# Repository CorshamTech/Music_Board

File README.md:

# SS-30 Music Board

This is a rough recreation of the Newtech Computer Systems model 68 music board.  No atttempt
was made to make it look exactly like the original, but it is 100% compatible and uses the
same components as the original.

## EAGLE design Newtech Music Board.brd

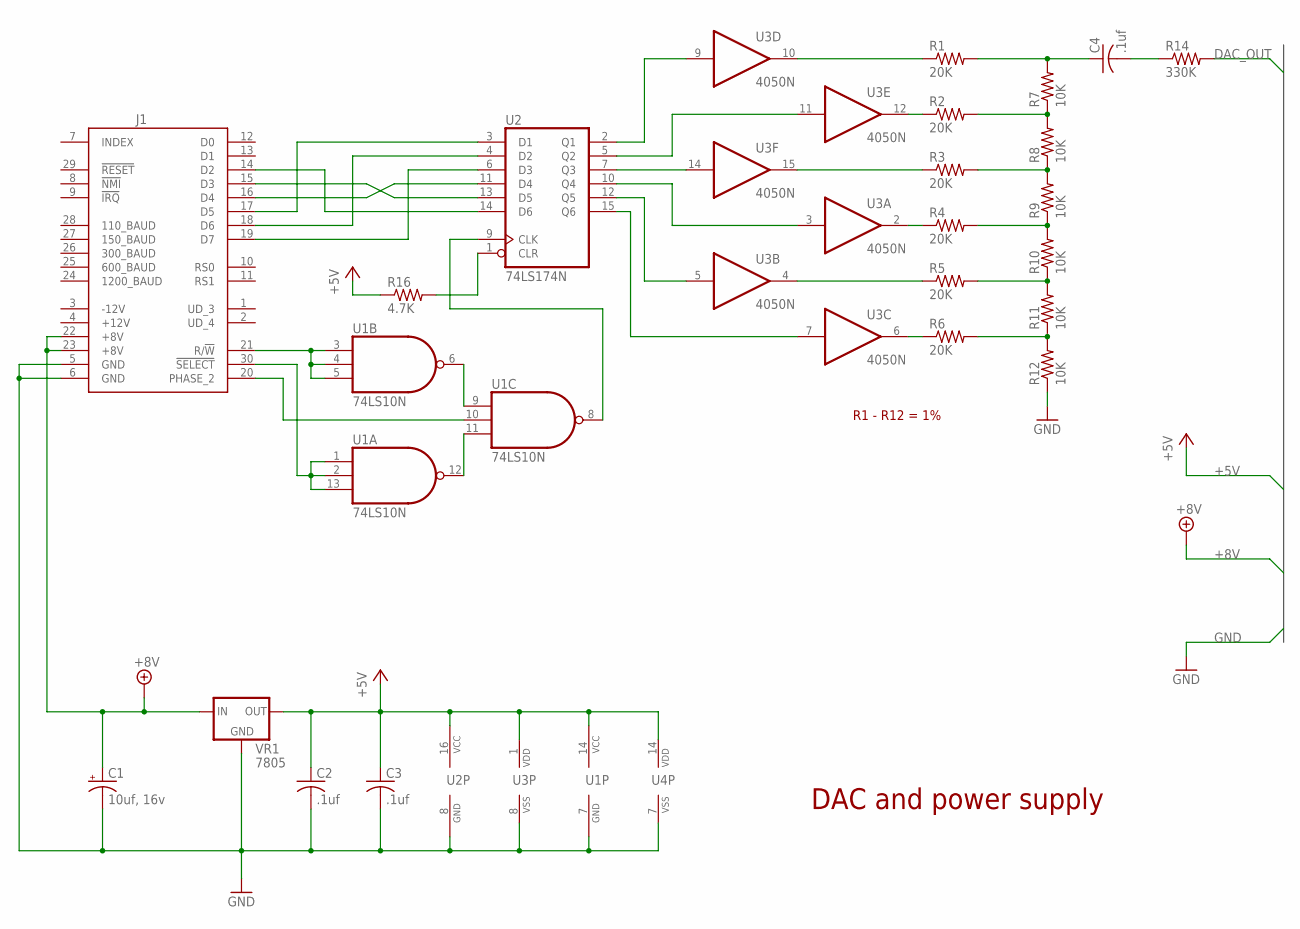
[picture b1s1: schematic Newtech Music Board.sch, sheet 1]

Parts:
C1: 10uf, 16v; E2,5-6
C2, C3: .1uf; C025-025X050
C4: .1uf; C025-024X044
J1: SS-30_BOARD_CONNECTOR
R1, R2, R3, R4, R5, R6: 20K; 0204/7
R7, R8, R9, R10, R11, R12: 10K; 0204/7
R14: 330K; 0204/7
R16: 4.7K; 0204/7
U1: 74LS10N; DIL14
U2: 74LS174N; DIL16
U3: 4050N; DIL16
U4: 4069N; DIL14
VR1: 7805; 78XXL

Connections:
!SELECT: J1.30 (!SELECT), U1.1 (I0), U1.2 (I1), U1.13 (I2)
+5V: C2.1, C3.1, R16.1, U1.14 (VCC), U2.16 (VCC), U3.1 (VDD), U4.14 (VDD), VR1.OUT
+8V: C1.+, J1.22 (+8V), J1.23 (+8V), VR1.IN; also elsewhere on the board
+12V: J1.4 (+12V)
-12V: J1.3 (-12V)
DAC_OUT: R14.2; also elsewhere on the board
GND: C1.-, C2.2, C3.2, J1.5 (GND), J1.6 (GND), R12.1, U1.7 (GND), U2.8 (GND), U3.8 (VSS), U4.7 (VSS), VR1.GND; also elsewhere on the board
unnamed: J1.19 (D7), U2.6 (D3)
unnamed: J1.18 (D6), U2.4 (D2)
unnamed: J1.17 (D5), U2.3 (D1)
unnamed: U1.6 (O), U1.9 (I0)
unnamed: U1.11 (I2), U1.12 (O)
unnamed: J1.16 (D4), U2.11 (D4)
unnamed: J1.15 (D3), U2.13 (D5)
unnamed: J1.14 (D2), U2.14 (D6)
unnamed: U2.2 (Q1), U3.9 (I)
unnamed: U2.5 (Q2), U3.11 (I)
unnamed: U2.7 (Q3), U3.14 (I)
unnamed: U2.10 (Q4), U3.3 (I)
unnamed: U2.12 (Q5), U3.5 (I)
unnamed: U2.15 (Q6), U3.7 (I)
unnamed: U1.8 (O), U2.9 (CLK)
unnamed: R16.2, U2.1 (CLR)
unnamed: R1.1, U3.10 (O)
unnamed: R2.1, U3.12 (O)
unnamed: R3.1, U3.15 (O)
unnamed: R4.1, U3.2 (O)
unnamed: R5.1, U3.4 (O)
unnamed: R6.1, U3.6 (O)
unnamed: R2.2, R7.1, R8.2
unnamed: R3.2, R8.1, R9.2
unnamed: R4.2, R9.1, R10.2
unnamed: R5.2, R10.1, R11.2
unnamed: R6.2, R11.1, R12.2
unnamed: C4.1, R1.2, R7.2
unnamed: C4.2, R14.1
PHASE2: J1.20 (PHASE_2), U1.10 (I1)
R/!W: J1.21 (R/!W), U1.3 (I0), U1.4 (I1), U1.5 (I2)

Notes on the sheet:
DAC and power supply
R1 - R12 = 1%

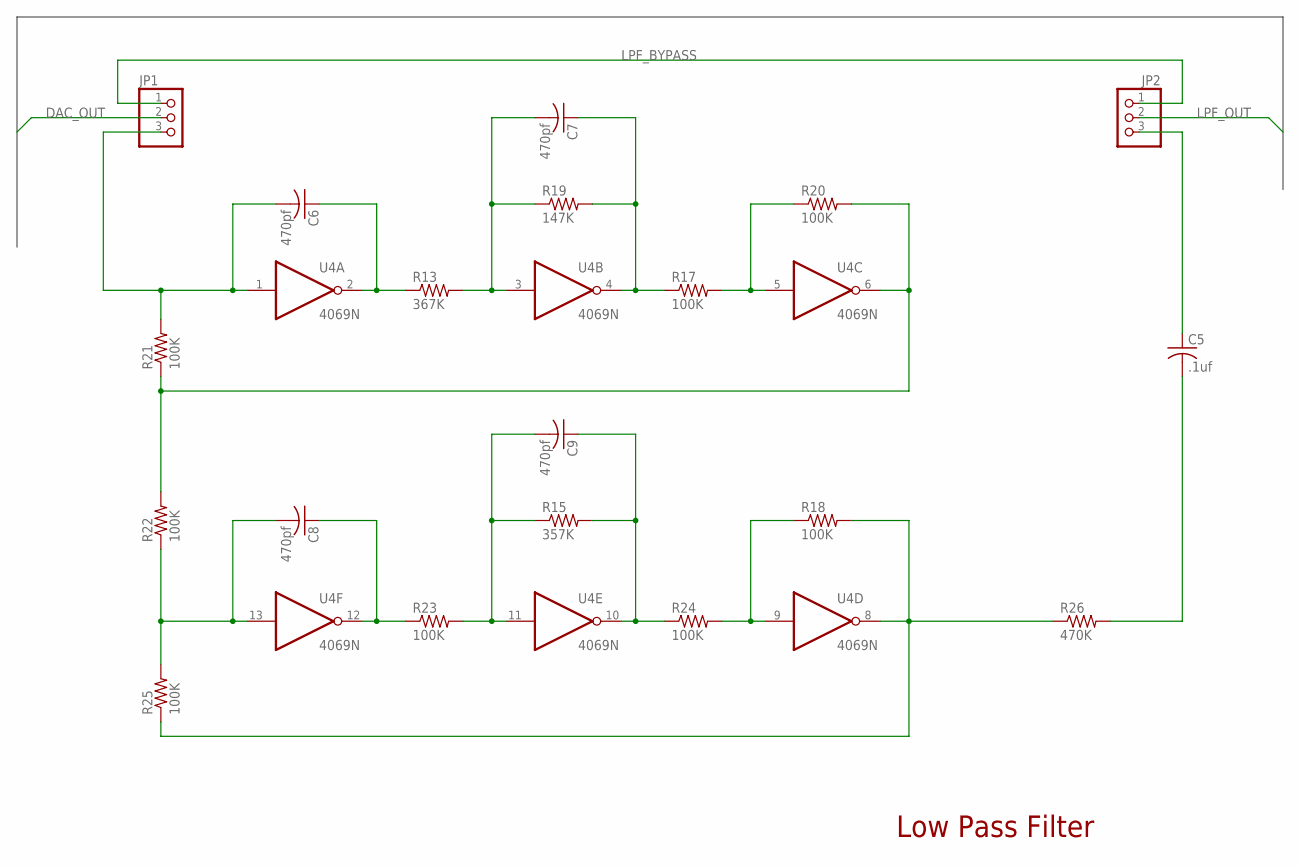
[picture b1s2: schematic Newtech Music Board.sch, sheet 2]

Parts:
C5: .1uf; C025-025X050
C6, C7, C8, C9: 470pf; C050-045X075
JP1, JP2: PINHD-1X3; 1X03
R13: 367K; 0204/7
R15: 357K; 0204/7
R17, R18, R20, R21, R22, R23, R24, R25: 100K; 0204/7
R19: 147K; 0204/7
R26: 470K; 0204/7
U4: 4069N; DIL14

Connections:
DAC_OUT: JP1.2; also elsewhere on the board
LPF_BYPASS: JP1.1, JP2.1
LPF_OUT: JP2.2; also elsewhere on the board
unnamed: C6.2, JP1.3, R21.2, U4.1 (I)
unnamed: C5.1, JP2.3
unnamed: C6.1, R13.1, U4.2 (O)
unnamed: C7.2, R13.2, R19.1, U4.3 (I)
unnamed: C7.1, R17.1, R19.2, U4.4 (O)
unnamed: R17.2, R20.1, U4.5 (I)
unnamed: R20.2, R21.1, R22.2, U4.6 (O)
unnamed: C8.1, R23.1, U4.12 (O)
unnamed: C9.2, R15.1, R23.2, U4.11 (I)
unnamed: C9.1, R15.2, R24.1, U4.10 (O)
unnamed: R18.1, R24.2, U4.9 (I)
unnamed: R18.2, R25.1, R26.1, U4.8 (O)
unnamed: C5.2, R26.2
unnamed: C8.2, R22.1, R25.2, U4.13 (I)

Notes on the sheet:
Low Pass Filter

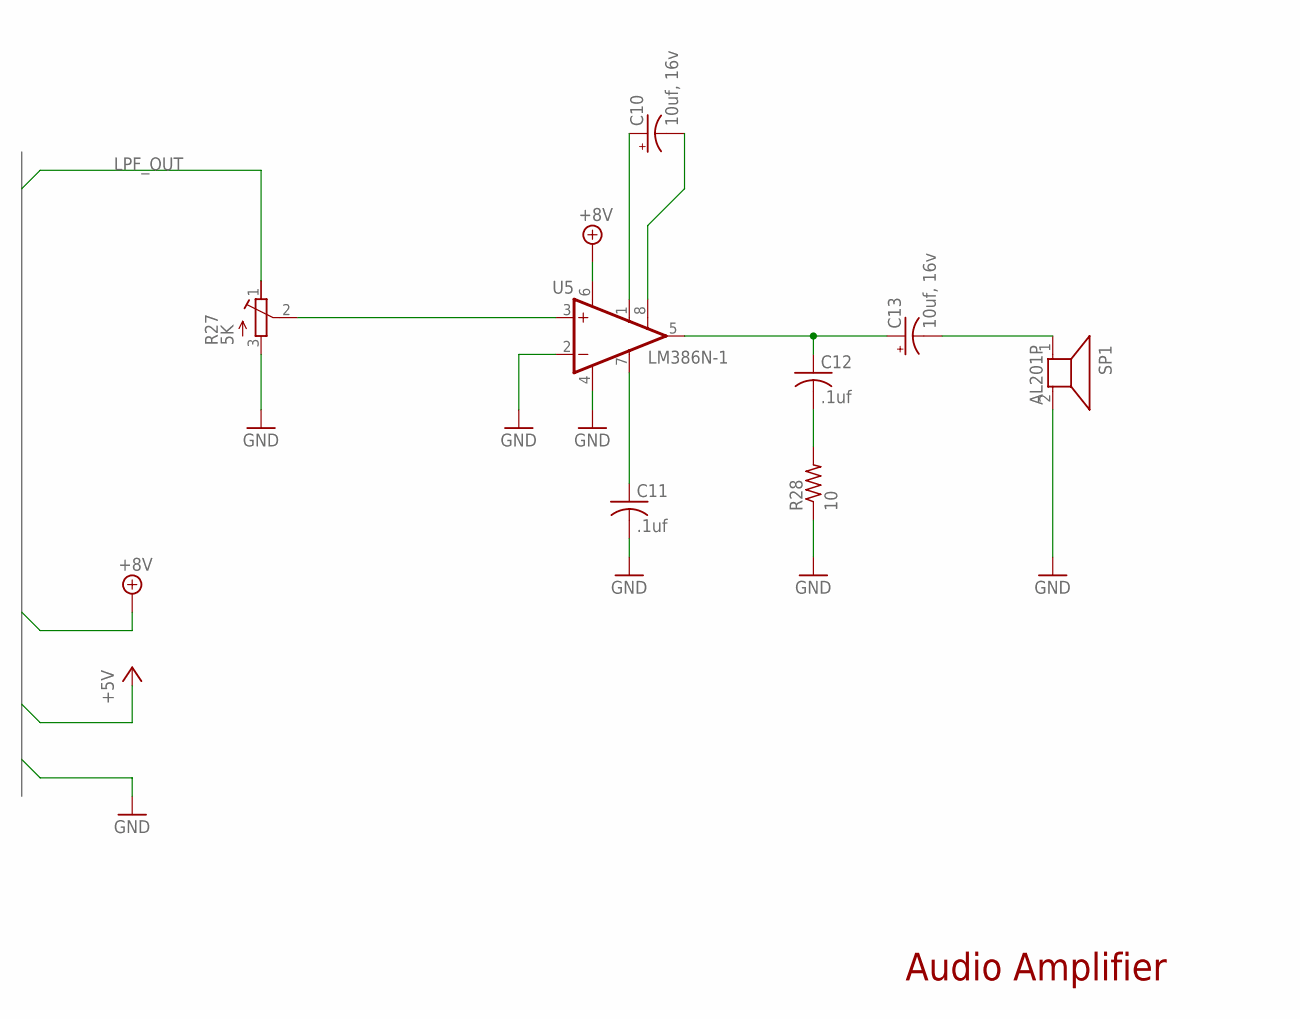
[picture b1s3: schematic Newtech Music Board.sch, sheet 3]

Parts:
C10, C13: 10uf, 16v; E2,5-6
C11, C12: .1uf; C025-025X050
R27: 5K; RTRIM43P
R28: 10; 0204/7
SP1: AL201P
U5: LM386N-1; DIL08

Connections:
+8V: U5.6 (VS); also elsewhere on the board
GND: C11.2, R27.3 (E), R28.1, SP1.2, U5.2 (-IN), U5.4 (GND); also elsewhere on the board
LPF_OUT: R27.1 (A); also elsewhere on the board
unnamed: C10.+, U5.1 (GAIN)
unnamed: R27.2 (S), U5.3 (+IN)
unnamed: C11.1, U5.7 (BYPASS)
unnamed: C10.-, U5.8 (GAIN)
unnamed: C12.1, C13.+, U5.5 (OUT)
unnamed: C13.-, SP1.1
unnamed: C12.2, R28.2

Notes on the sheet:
Audio Amplifier

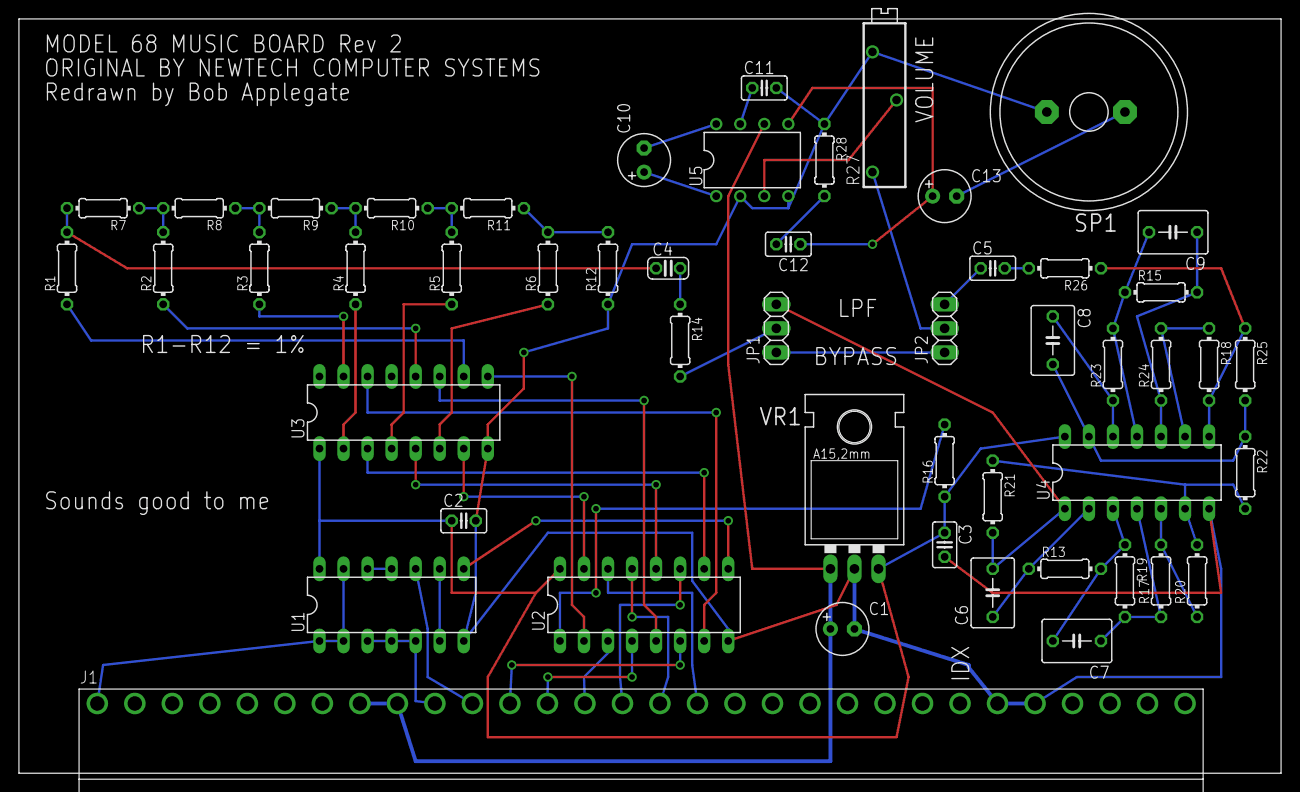
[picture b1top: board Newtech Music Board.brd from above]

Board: 2 copper layers, 133.3 x 79.7 mm, 51 parts (0 on the bottom side), 59 nets.

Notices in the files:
parts and their libraries:
SparkFun: Licensing: CC v3.0 Share-Alike You are welcome to use this library for commercial purposes.
